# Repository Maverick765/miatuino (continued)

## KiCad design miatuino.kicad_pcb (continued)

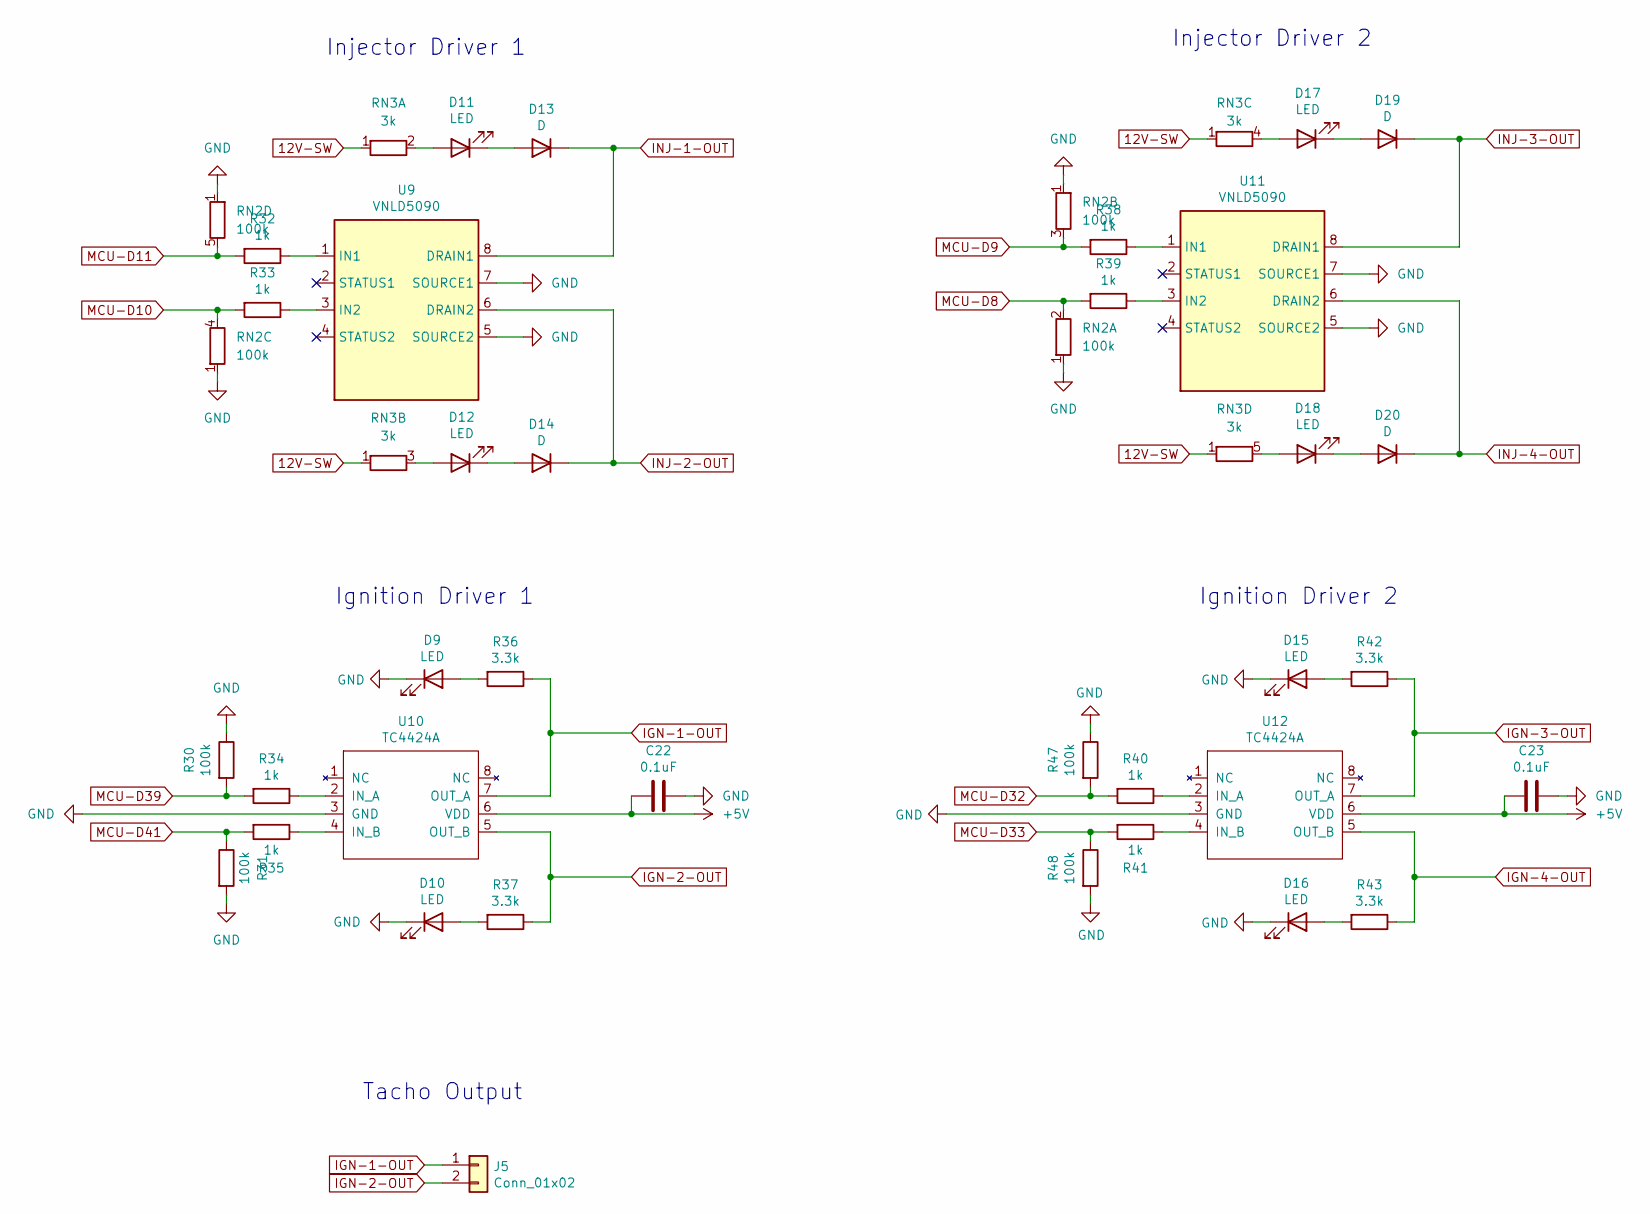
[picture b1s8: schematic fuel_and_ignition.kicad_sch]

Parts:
C22, C23: 0.1uF; C_Disc_D4.7mm_W2.5mm_P5.00mm; Manufacturer_Part_Number CC0805KRX7R9BB104; Digikey Part Number 311-1140-1-ND
D9, D10, D11, D12, D15, D16, D17, D18: LED; LED_D3.0mm; Manufacturer_Part_Number LH R974-LP-1; Digikey Part Number 475-1415-1-ND
D13, D14, D19, D20: D; D_T-1_P5.08mm_Horizontal; Manufacturer_Part_Number 1N4448WX-TP; Digikey Part Number 1N4448WXTPMSCT-ND
J5: Conn_01x02; PinHeader_1x02_P2.54mm_Vertical
R30, R31, R47, R48: 100k; R_Axial_DIN0207_L6.3mm_D2.5mm_P7.62mm_Horizontal; Manufacturer_Part_Number RC0805FR-071KL; Digikey Part Number 311-1.00KCRCT-ND
R32, R33, R34, R35, R38, R39, R40, R41: 1k; R_Axial_DIN0207_L6.3mm_D2.5mm_P7.62mm_Horizontal; Manufacturer_Part_Number RC0805FR-071KL; Digikey Part Number 311-1.00KCRCT-ND
R36, R37, R42, R43: 3.3k; R_Axial_DIN0207_L6.3mm_D2.5mm_P7.62mm_Horizontal; Manufacturer_Part_Number RC0805FR-072K4L; Digikey Part Number 311-2.40KCRCT-ND
RN2: 100k; R_Array_SIP5
RN3: 3k; R_Array_SIP5
U9, U11: VNLD5090; SO-8_3.9x4.9mm_P1.27mm; Manufacturer_Part_Number VNLD5090-E; Digikey Part Number 497-18682-ND
U10, U12: TC4424A; SOIC-8_3.9x4.9mm_P1.27mm; Manufacturer_Part_Number TC4424AVOA; Digikey Part Number TC4424AVOA-ND

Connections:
12V-SW: RN3.1 (R1); also elsewhere on the board
+5V: C22.2, C23.2, U10.6 (VDD), U12.6 (VDD); also elsewhere on the board
GND: C22.1, C23.1, D9.1 (K), D10.1 (K), D15.1 (K), D16.1 (K), R30.1, R31.2, R47.1, R48.2, RN2.1 (R1), U9.5 (SOURCE2), U9.7 (SOURCE1), U10.3 (GND), U11.5 (SOURCE2), U11.7 (SOURCE1), U12.3 (GND); also elsewhere on the board
IGN-1-OUT: J5.1, R36.1, U10.7 (OUT_A); also elsewhere on the board
IGN-2-OUT: J5.2, R37.1, U10.5 (OUT_B); also elsewhere on the board
IGN-3-OUT: R42.1, U12.7 (OUT_A)
IGN-4-OUT: R43.1, U12.5 (OUT_B)
INJ-1-OUT: D13.1 (K), U9.8 (DRAIN1); also elsewhere on the board
INJ-2-OUT: D14.1 (K), U9.6 (DRAIN2); also elsewhere on the board
INJ-3-OUT: D19.1 (K), U11.8 (DRAIN1); also elsewhere on the board
INJ-4-OUT: D20.1 (K), U11.6 (DRAIN2); also elsewhere on the board
MCU-D8: R39.2, RN2.2 (R1.2); also elsewhere on the board
MCU-D9: R38.2, RN2.3 (R2.2); also elsewhere on the board
MCU-D10: R33.2, RN2.4 (R3.2); also elsewhere on the board
MCU-D11: R32.2, RN2.5 (R4.2); also elsewhere on the board
MCU-D32: R40.2, R47.2; also elsewhere on the board
MCU-D33: R41.2, R48.1; also elsewhere on the board
MCU-D39: R30.2, R34.2; also elsewhere on the board
MCU-D41: R31.1, R35.2; also elsewhere on the board
unnamed: D9.2 (A), R36.2
unnamed: D10.2 (A), R37.2
unnamed: D11.2 (A), RN3.2 (R1.2)
unnamed: D11.1 (K), D13.2 (A)
unnamed: D12.2 (A), RN3.3 (R2.2)
unnamed: D12.1 (K), D14.2 (A)
unnamed: D15.2 (A), R42.2
unnamed: D16.2 (A), R43.2
unnamed: D17.2 (A), RN3.4 (R3.2)
unnamed: D17.1 (K), D19.2 (A)
unnamed: D18.2 (A), RN3.5 (R4.2)
unnamed: D18.1 (K), D20.2 (A)
unnamed: R32.1, U9.1 (IN1)
unnamed: R33.1, U9.3 (IN2)
unnamed: R34.1, U10.2 (IN_A)
unnamed: R35.1, U10.4 (IN_B)
unnamed: R38.1, U11.1 (IN1)
unnamed: R39.1, U11.3 (IN2)
unnamed: R40.1, U12.2 (IN_A)
unnamed: R41.1, U12.4 (IN_B)

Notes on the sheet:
Tacho Output
Injector Driver 2
Ignition Driver 1
Injector Driver 1
Ignition Driver 2

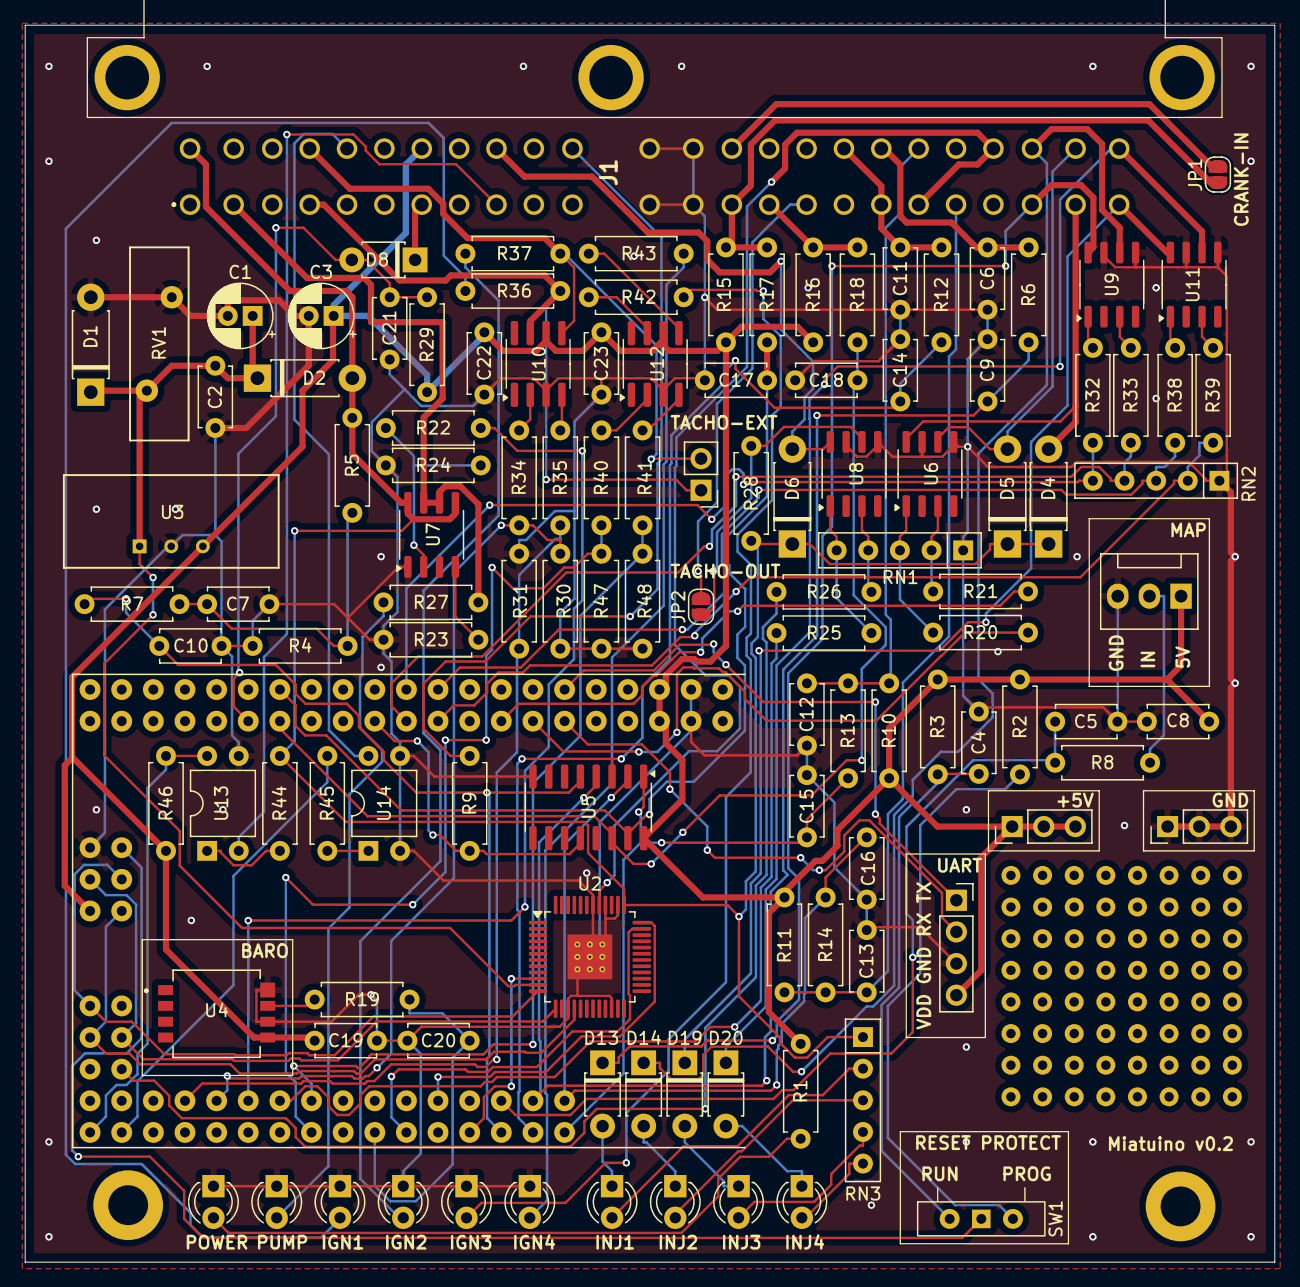
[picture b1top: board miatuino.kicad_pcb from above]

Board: 2 copper layers, 100.3 x 99.3 mm, 120 parts (0 on the bottom side), 100 nets.
